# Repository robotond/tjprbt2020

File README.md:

# tjprbt2020
TJPRBT2020 is an ESP32-WROOM based 3D printed robotic car with actuators and sensors

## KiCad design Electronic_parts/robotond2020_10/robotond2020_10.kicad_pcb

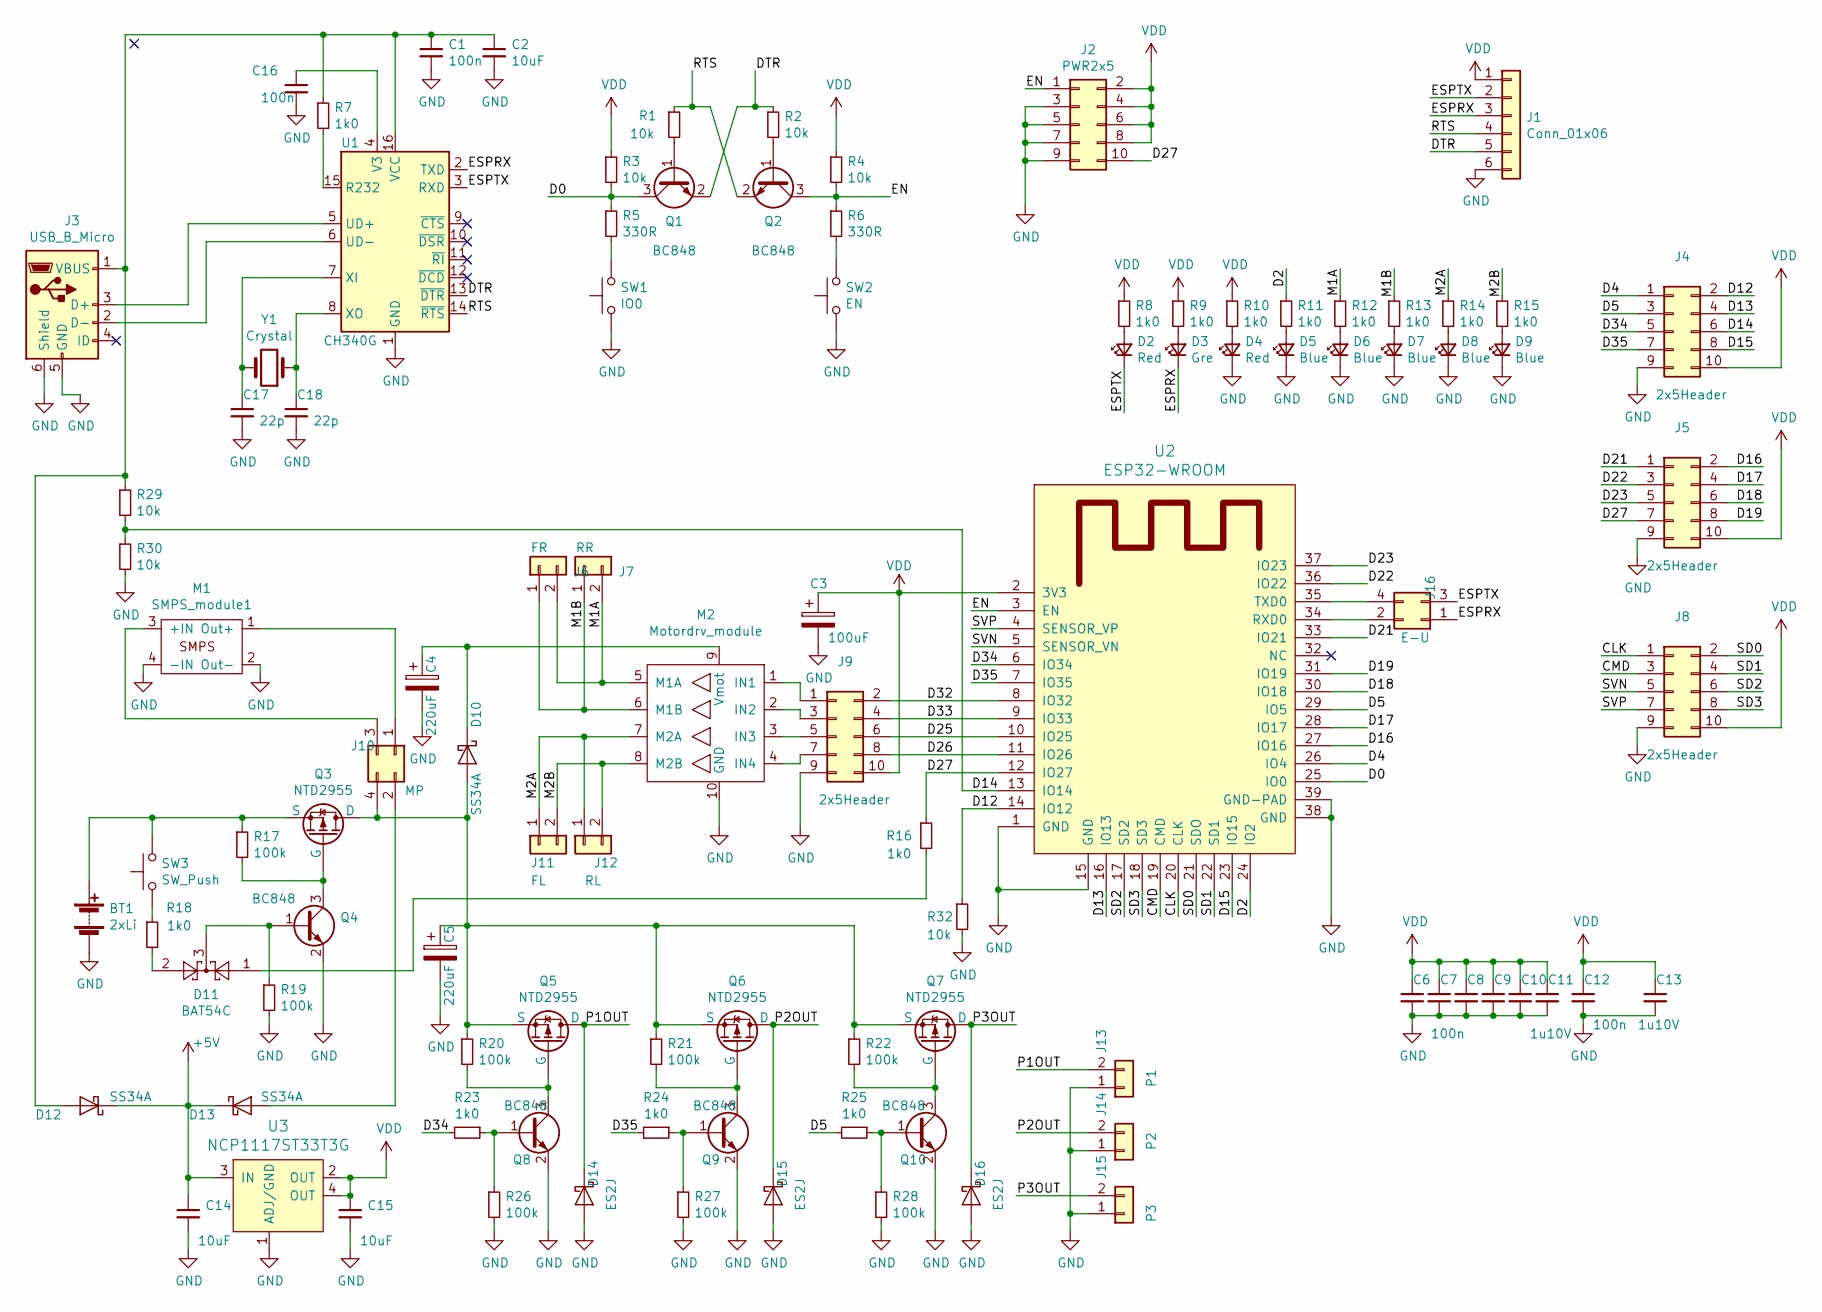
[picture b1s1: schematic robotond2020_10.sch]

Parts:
BT1: 2xLi; JST_XH_B02B-XH-A_1x02_P2.50mm_Vertical
C1, C6, C7, C8, C9, C10, C12, C16: 100n; C_0805_2012Metric_Pad1.15x1.40mm_HandSolder
C2, C14, C15: 10uF; C_0805_2012Metric_Pad1.15x1.40mm_HandSolder
C3: 100uF; CP_Elec_6.3x7.7
C4, C5: 220uF; CP_Elec_6.3x7.7
C11, C13: 1u10V; C_0805_2012Metric_Pad1.15x1.40mm_HandSolder
C17, C18: 22p; C_0805_2012Metric_Pad1.15x1.40mm_HandSolder
D2, D4: Red; D_0603_1608Metric_Pad1.05x0.95mm_HandSolder
D3: Gre; D_0603_1608Metric_Pad1.05x0.95mm_HandSolder
D5, D6, D7, D8, D9: Blue; D_0603_1608Metric_Pad1.05x0.95mm_HandSolder
D10, D12, D13: SS34A; D_SMB
D11: BAT54C; SOT-23
D14, D15, D16: ES2J; D_SMB
J1: Conn_01x06; JST_XH_B06B-XH-A_1x06_P2.50mm_Vertical
J2: PWR2x5; PinHeader_2x05_P2.54mm_Vertical
J3: USB_B_Micro; USB_Micro_B_Female_1050170001
J4, J5, J8, J9: 2x5Header; PinHeader_2x05_P2.54mm_Vertical
J6: FR; JST_XH_B02B-XH-A_1x02_P2.50mm_Vertical
J7: RR; JST_XH_B02B-XH-A_1x02_P2.50mm_Vertical
J10: MP; PinHeader_2x02_P2.54mm_Vertical
J11: FL; JST_XH_B02B-XH-A_1x02_P2.50mm_Vertical
J12: RL; JST_XH_B02B-XH-A_1x02_P2.50mm_Vertical
J13: P1; JST_XH_B02B-XH-A_1x02_P2.50mm_Vertical
J14: P2; JST_XH_B02B-XH-A_1x02_P2.50mm_Vertical
J15: P3; JST_XH_B02B-XH-A_1x02_P2.50mm_Vertical
J16: E-U; PinHeader_2x02_P2.54mm_Vertical
M1: SMPS_module1; MP2307MOD
M2: Motordrv_module; MX1608MOD
Q1, Q2, Q4, Q8, Q9, Q10: BC848; SOT-23
Q3, Q5, Q6, Q7: NTD2955; TO-252-3_TabPin4
R1, R2, R3, R4, R29, R30, R32: 10k; R_0805_2012Metric_Pad1.15x1.40mm_HandSolder
R5, R6: 330R; R_0805_2012Metric_Pad1.15x1.40mm_HandSolder
R7, R8, R9, R10, R11, R12, R13, R14, R15, R16, R18, R23, R24, R25: 1k0; R_0805_2012Metric_Pad1.15x1.40mm_HandSolder
R17, R19, R20, R21, R22, R26, R27, R28: 100k; R_0805_2012Metric_Pad1.15x1.40mm_HandSolder
SW1: IO0; SW_SPST_FSMSM
SW2: EN; SW_SPST_FSMSM
SW3: SW_Push; SW_SPST_FSMSM
U1: CH340G; SOIC-16_3.9x9.9mm_P1.27mm
U2: ESP32-WROOM; ESP32-WROOM-32
U3: NCP1117ST33T3G; SOT-223; MPN NCP1117ST33T3G; Digi-Key_PN NCP1117ST33T3GOSCT-ND
Y1: Crystal; Crystal_SMD_HC49-SD

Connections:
+5V: C14.1, D12.1 (K), D13.1 (K), U3.3 (IN)
/CLK: J8.1, U2.20 (CLK)
/CMD: J8.3, U2.19 (CMD)
/D0: Q1.3 (C), R3.2, R5.1, U2.25 (IO0)
/D2: R11.1, U2.24 (IO2)
/D4: J4.1, U2.26 (IO4)
/D5: J4.3, R25.2, U2.29 (IO5)
/D12: J4.2, R32.1, U2.14 (IO12)
/D13: J4.4, U2.16 (IO13)
/D14: J4.6, R29.2, R30.1, U2.13 (IO14)
/D15: J4.8, U2.23 (IO15)
/D16: J5.2, U2.27 (IO16)
/D17: J5.4, U2.28 (IO17)
/D18: J5.6, U2.30 (IO18)
/D19: J5.8, U2.31 (IO19)
/D21: J5.1, U2.33 (IO21)
/D22: J5.3, U2.36 (IO22)
/D23: J5.5, U2.37 (IO23)
/D25: J9.6, U2.10 (IO25)
/D26: J9.8, U2.11 (IO26)
/D27: J2.10, J5.7, R16.1, U2.12 (IO27)
/D32: J9.2, U2.8 (IO32)
/D33: J9.4, U2.9 (IO33)
/D34: J4.5, R23.2, U2.6 (IO34)
/D35: J4.7, R24.2, U2.7 (IO35)
/DTR: J1.5, Q1.2 (E), R2.1, U1.13 (~DTR)
/EN: J2.1, Q2.3 (C), R4.2, R6.1, U2.3 (EN)
/ESPRX: D3.1 (K), J1.3, J16.1, U1.2 (TXD)
/ESPTX: D2.1 (K), J1.2, J16.3, U1.3 (RXD)
/M1A: J6.2, J7.2, M2.5 (M1A), R12.1
/M1B: J6.1, J7.1, M2.6 (M1B), R13.1
/M2A: J11.1, J12.1, M2.7 (M2A), R14.1
/M2B: J11.2, J12.2, M2.8 (M2B), R15.1
/P1OUT: D14.1 (K), J13.2, Q5.4 (D)
/P2OUT: D15.1 (K), J14.2, Q6.4 (D)
/P3OUT: D16.1 (K), J15.2, Q7.4 (D)
/RTS: J1.4, Q2.2 (E), R1.1, U1.14 (~RTS)
/SD0: J8.2, U2.21 (SDO)
/SD1: J8.4, U2.22 (SD1)
/SD2: J8.6, U2.17 (SD2)
/SD3: J8.8, U2.18 (SD3)
/SVN: J8.5, U2.5 (SENSOR_VN)
/SVP: J8.7, U2.4 (SENSOR_VP)
GND: BT1.2 (-), C1.2, C2.2, C3.2, C4.2, C5.2, C6.2, C7.2, C8.2, C9.2, C10.2, C11.2, C12.2, C13.2, C14.2, C15.2, C16.2, C17.2, C18.2, D4.1 (K), D5.1 (K), D6.1 (K), D7.1 (K), D8.1 (K), D9.1 (K), D14.2 (A), D15.2 (A), D16.2 (A), J1.6, J2.3, J2.5, J2.7, J2.9, J3.5 (GND), J3.6 (Shield), J4.9, J5.9, J8.9, J9.9, J13.1, J14.1, J15.1, M1.2 (Out-), M1.4 (-IN), M2.10 (GND), Q4.2 (E), Q8.2 (E), Q9.2 (E), Q10.2 (E), R19.2, R26.2, R27.2, R28.2, R30.2, R32.2, SW1.1, SW2.1, U1.1 (GND), U2.1 (GND), U2.15 (GND), U2.38 (GND), U2.39 (GND-PAD), U3.1 (ADJ/GND)
unnamed: BT1.1 (+), Q3.3 (S), R17.1, SW3.2
unnamed: C1.1, C2.1, D12.2 (A), J3.1 (VBUS), R7.1, R29.1, U1.16 (VCC)
unnamed: C4.1, D10.1 (K), M2.9 (Vmot)
unnamed: C5.1, D10.2 (A), J10.4, Q3.4 (D), Q5.3 (S), Q6.3 (S), Q7.3 (S), R20.1, R21.1, R22.1
unnamed: C16.1, U1.4 (V3)
unnamed: C17.1, U1.7 (XI), Y1.2
unnamed: C18.1, U1.8 (XO), Y1.1
unnamed: D2.2 (A), R8.2
unnamed: D3.2 (A), R9.2
unnamed: D4.2 (A), R10.2
unnamed: D5.2 (A), R11.2
unnamed: D6.2 (A), R12.2
unnamed: D7.2 (A), R13.2
unnamed: D8.2 (A), R14.2
unnamed: D9.2 (A), R15.2
unnamed: D11.1, R16.2
unnamed: D11.2, R18.2
unnamed: D11.3, Q4.1 (B), R19.1
unnamed: D13.2 (A), J10.2
unnamed: J3.2 (D-), U1.6 (UD-)
unnamed: J3.3 (D+), U1.5 (UD+)
unnamed: J9.1, M2.1 (IN1)
unnamed: J9.3, M2.2 (IN2)
unnamed: J9.5, M2.3 (IN3)
unnamed: J9.7, M2.4 (IN4)
unnamed: J10.1, M1.1 (Out+)
unnamed: J10.3, M1.3 (+IN)
unnamed: J16.2, U2.34 (RXD0)
unnamed: J16.4, U2.35 (TXD0)
unnamed: Q1.1 (B), R1.2
unnamed: Q2.1 (B), R2.2
unnamed: Q3.1 (G), Q4.3 (C), R17.2
unnamed: Q5.1 (G), Q8.3 (C), R20.2
unnamed: Q6.1 (G), Q9.3 (C), R21.2
unnamed: Q8.1 (B), R23.1, R26.1
unnamed: Q9.1 (B), R24.1, R27.1
unnamed: Q10.1 (B), R25.1, R28.1
unnamed: Q7.1 (G), Q10.3 (C), R22.2
unnamed: R5.2, SW1.2
unnamed: R6.2, SW2.2
unnamed: R7.2, U1.15 (R232)
unnamed: R18.1, SW3.1
VDD: C3.1, C6.1, C7.1, C8.1, C9.1, C10.1, C11.1, C12.1, C13.1, C15.1, J1.1, J2.2, J2.4, J2.6, J2.8, J4.10, J5.10, J8.10, J9.10, R3.1, R4.1, R8.1, R9.1, R10.1, U2.2 (3V3), U3.2 (OUT), U3.4 (OUT)

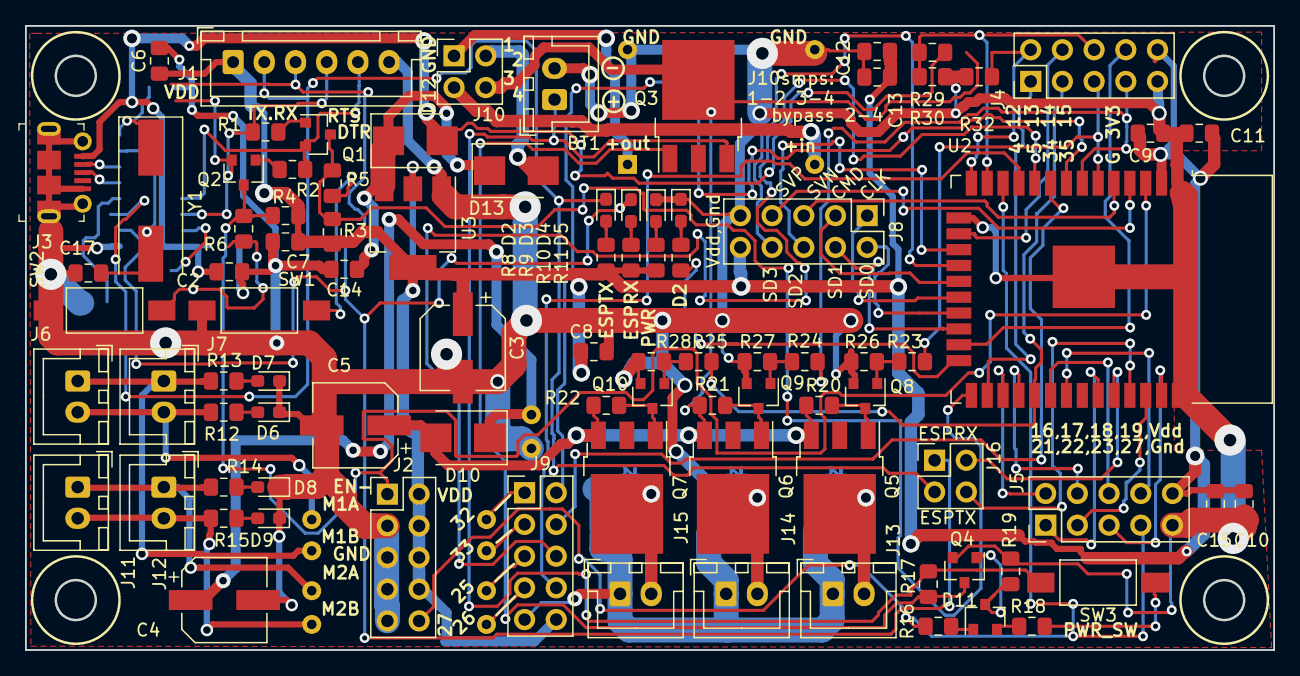
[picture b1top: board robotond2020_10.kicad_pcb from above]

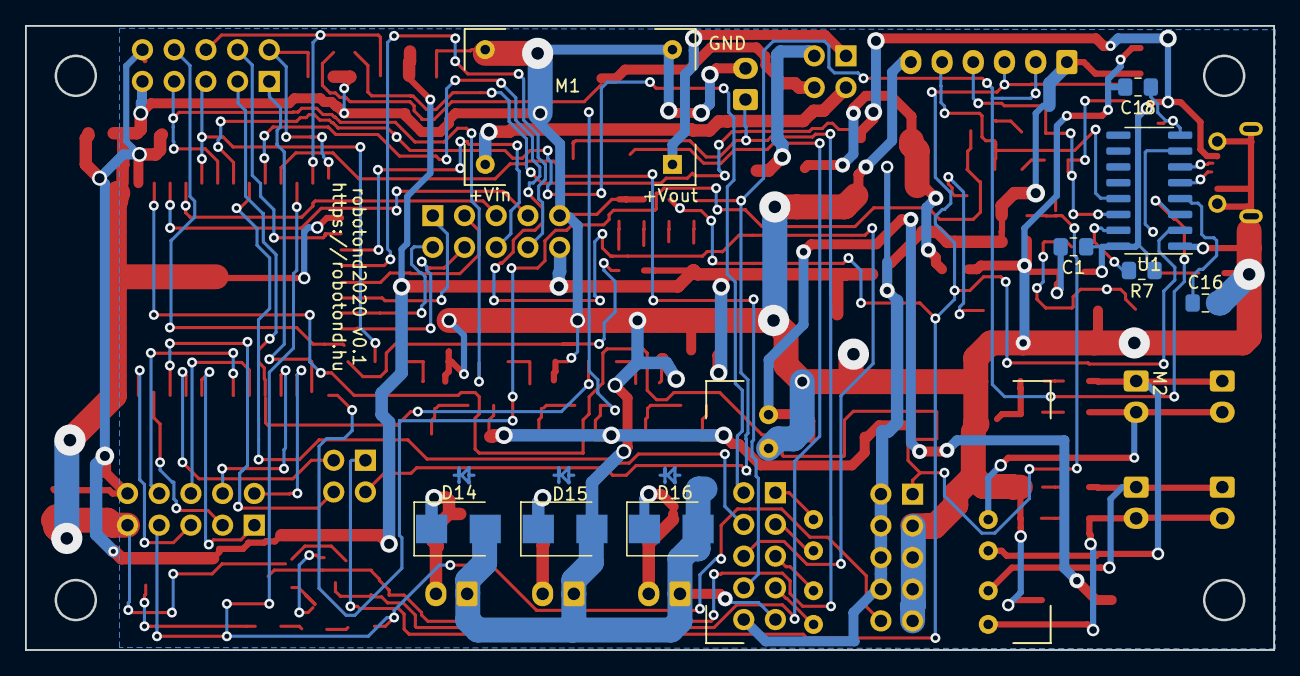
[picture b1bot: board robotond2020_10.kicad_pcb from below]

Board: 2 copper layers, 100.0 x 50.0 mm, 100 parts (10 on the bottom side), 87 nets.

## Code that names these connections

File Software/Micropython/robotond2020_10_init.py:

from machine import Pin
led=Pin(2,Pin.OUT) #onboard LED
pwr=Pin(27,Pin.OUT) #PWR_ON pin
M1A=Pin(32,Pin.OUT) #Motor conrtoller pins as appear on the motor controller board
M1B=Pin(33,Pin.OUT)
M2A=Pin(25,Pin.OUT)
M2B=Pin(26,Pin.OUT)

pwr.value(True)
led.value(True)

M1A.value(True)
M2A.value(True)
M1B.value(True)
M2B.value(True)

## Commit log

2020-10-30 After several days of work I decided to keep my project on GITHUB. This is the initial commit when I add all relevant files. This is a stub, not a finished polished product.
2020-10-30 Adde micropython intitializing code which enables to use power on button. The code assumes that the ESP32 micropython firmware was previously installed on the module.
2020-10-30 Added micropython intitializing code which enables to use the power on button. Also some motor controller initialization code was included. The code assumes that the ESP32 micropython firmware was pr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
